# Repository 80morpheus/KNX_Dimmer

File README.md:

# KNX Dimmer
up to 16 channels possible
depends on the configuration

W = Single
CW = Cold/Warm White
RGB = RGB
RGBW = RGB+White
RGBCW = RGB+Cold/Warm White

Possible outputs:
3X  RGBCW
or
4x  RGBW
or
5X  RGB
or
8X  CW
or
16X W

CH1  S CW RGB RGBW RGBCW 
CH2  S CW RGB RGBW RGBCW 
CH3  S CW RGB RGBW RGBCW 
CH4  S CW RGB RGBW  
CH5  S CW RGB  
CH6  S CW      
CH7  S CW      
CH8  S CW      
CH9  S        
CH10 S        
CH11 S        
CH12 S        
CH13 S        
CH14 S        
CH15 S        
CH16 S         

# dimm bedingung
wenn abs oder rel dimmen dann nur bis min wert
wenn ausschalten, dann aus und optional farbwerte auf standard zurück setzen

single ist easy -> zwischen min und max

cw -> ginge auch zwischen min und max
      cw werte ??? müßte zwei min um evtl aus zu vermeiden
      ets eingabe farbtemp für c + w
      ets regler für temperatur gibt prozentual an welche der beiden wo steht
      links = nur c wird gesteuert und w ist dann 0
      mitte = beide selber wert
      rechts = nur w wird gesteuert und c ist dann 0

rgb -> dimmt nur von 0 bis setpoint
      min wert macht keinen sinn da dann zu komplizierte berechnungen

rgbw -> siehe rgb
      wie wird w behandelt ??? einzelnes licht objekt

rgbcw -> wie wird c und w behandelt ??? einzelnes licht objekt
      ets eingabe farbtemp für c + w
      ets standard wert - wird nach aus wieder aktiv ja/nein
      rgb dimmt von 0 bis setpoint

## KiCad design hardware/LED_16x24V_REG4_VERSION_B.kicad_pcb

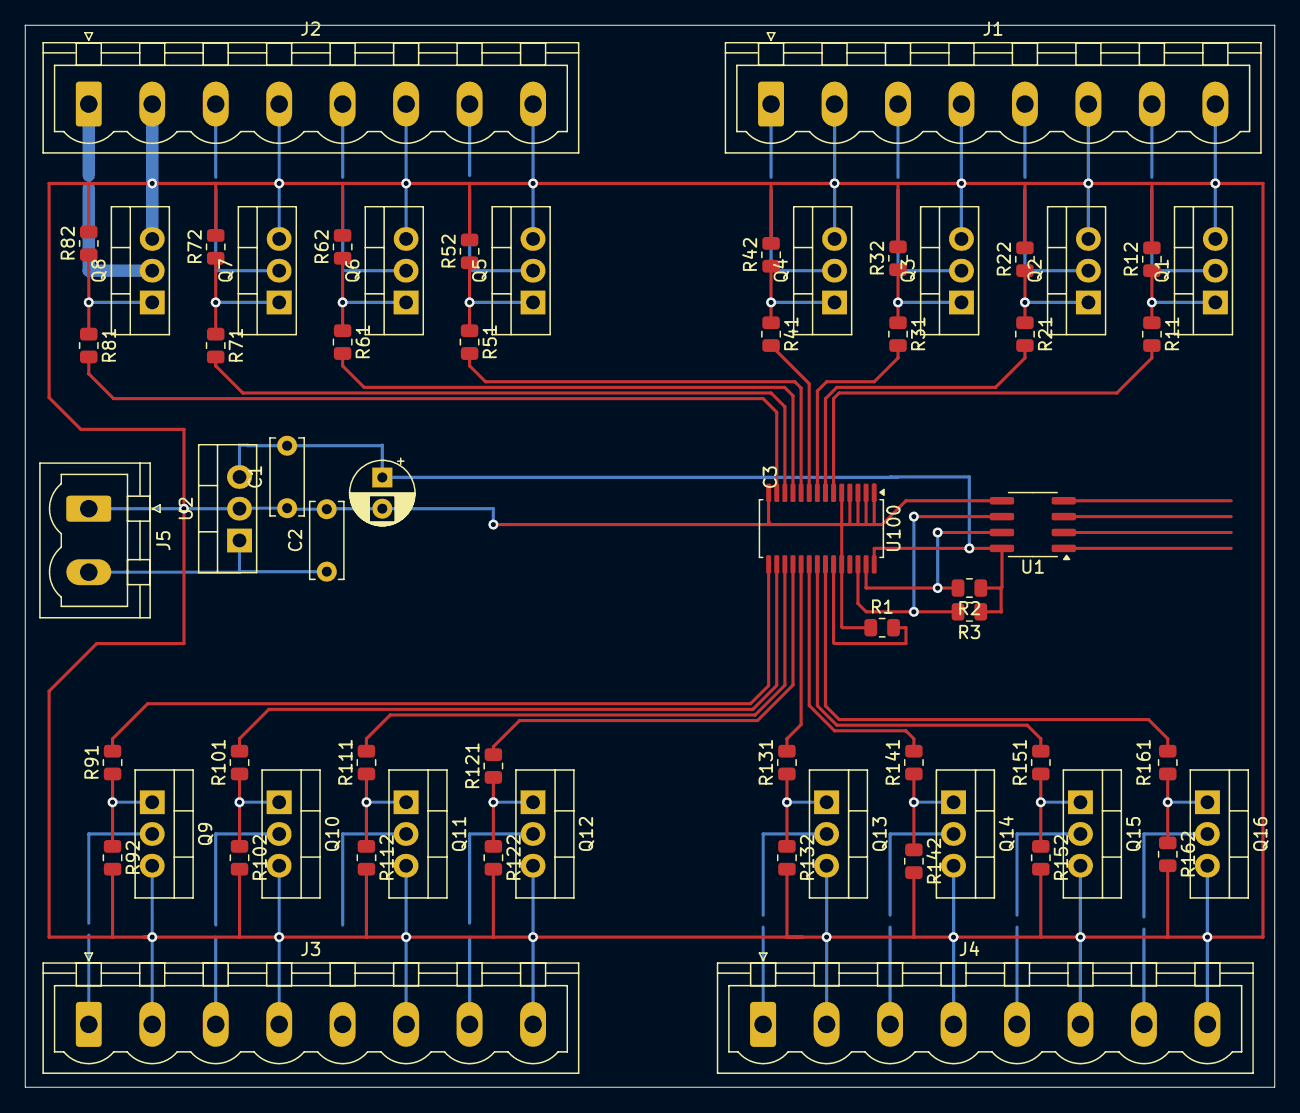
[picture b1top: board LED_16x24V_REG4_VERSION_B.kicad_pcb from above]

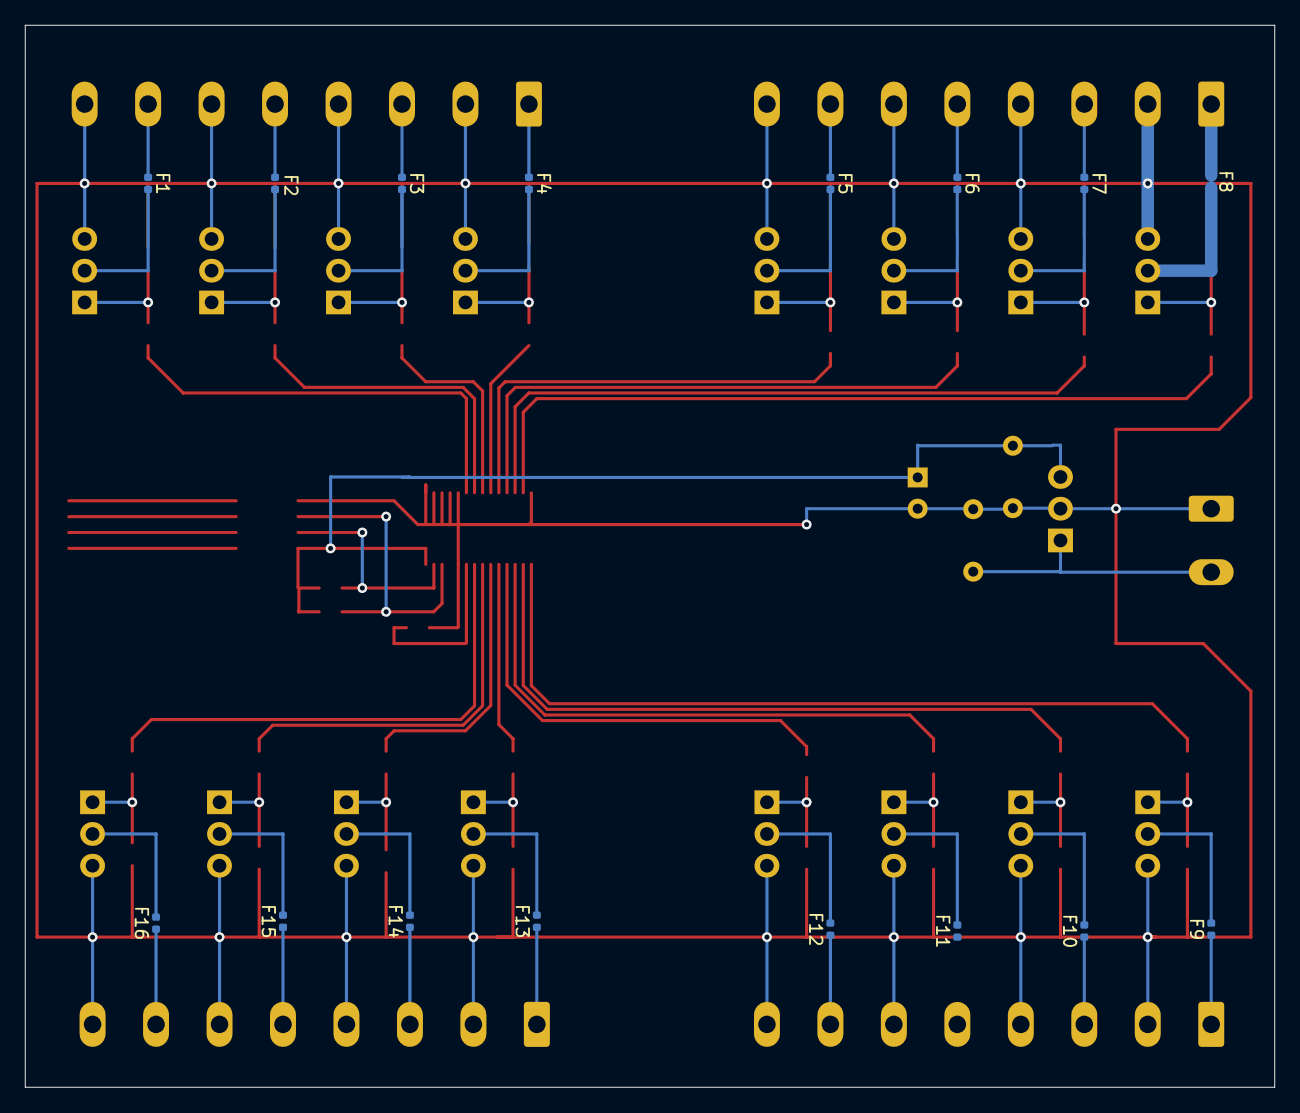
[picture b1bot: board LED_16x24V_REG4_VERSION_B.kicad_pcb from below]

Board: 2 copper layers, 100.0 x 85.0 mm, 78 parts (16 on the bottom side), 66 nets.

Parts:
C1: 0.1µF; C_Disc_D6.0mm_W2.5mm_P5.00mm
C2: 0.33µF; C_Disc_D6.0mm_W2.5mm_P5.00mm
C3: 100µF; CP_Radial_D5.0mm_P2.50mm
F1, F2, F3, F4, F5, F6, F7, F8, F9, F10, F11, F12, F13, F14, F15, F16: Fuse; Fuse_0402_1005Metric
J1, J2, J3, J4: Conn_01x08; PhoenixContact_MSTBVA_2,5_8-G-5,08_1x08_P5.08mm_Vertical
J5: Conn_01x02; PhoenixContact_MSTBVA_2,5_2-G-5,08_1x02_P5.08mm_Vertical
Q1, Q2, Q3, Q4, Q5, Q6, Q7, Q8, Q9, Q10, Q11, Q12, Q13, Q14, Q15, Q16: IRF3205; TO-220-3_Vertical
R1, R11, R12, R21, R22, R31, R32, R41, R42, R51, R52, R61, R62, R71, R72, R81, R82, R91, R92, R101, R102, R111, R112, R121, R122, R131, R132, R141, R142, R151, R152, R161, R162: R; R_0805_2012Metric
R2, R3: 10k; R_0805_2012Metric
U1: ADuM1250; SOIC-8_3.9x4.9mm_P1.27mm
U2: L7806; TO-220-3_Vertical
U100: PCA9685PW; TSSOP-28_4.4x9.7mm_P0.65mm

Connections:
GND_LED: C1.1, C2.2, C3.2, F7.1, F7.2, F8.1, F8.2, J1.2, J1.4, J1.6, J1.8, J2.1, J2.2, J2.3, J2.4, J2.6, J2.8, J3.2, J3.4, J3.6, J3.8, J4.2, J4.4, J4.6, J4.8, J5.1, Q1.3 (S), Q2.3 (S), Q3.3 (S), Q4.3 (S), Q5.3 (S), Q6.3 (S), Q7.2 (D), Q7.3 (S), Q8.2 (D), Q8.3 (S), Q9.3 (S), Q10.3 (S), Q11.3 (S), Q12.3 (S), Q13.3 (S), Q14.3 (S), Q15.3 (S), Q16.3 (S), R1.1, R12.2, R22.2, R32.2, R42.2, R52.2, R62.2, R72.2, R82.2, R92.2, R102.2, R112.2, R122.2, R132.2, R142.2, R152.2, R162.2, U1.5 (GND2), U2.2 (GND), U100.1 (A0), U100.2 (A1), U100.3 (A2), U100.4 (A3), U100.5 (A4), U100.14 (VSS), U100.24 (A5)
unnamed: F4.1, J1.1
unnamed: F3.1, J1.3
unnamed: F2.1, J1.5
unnamed: F1.1, J1.7
unnamed: F6.1, J2.5
unnamed: F5.1, J2.7
unnamed: F9.1, J3.1
unnamed: F10.1, J3.3
unnamed: F11.1, J3.5
unnamed: F12.1, J3.7
unnamed: F13.1, J4.1
unnamed: F14.1, J4.3
unnamed: F15.1, J4.5
unnamed: F16.1, J4.7
unnamed: C2.1, J5.2, U2.1 (IN)
unnamed: F1.2, Q1.2 (D)
unnamed: Q1.1 (G), R11.1, R12.1
unnamed: F2.2, Q2.2 (D)
unnamed: Q2.1 (G), R21.1, R22.1
unnamed: F3.2, Q3.2 (D)
unnamed: Q3.1 (G), R31.1, R32.1
unnamed: F4.2, Q4.2 (D)
unnamed: Q4.1 (G), R41.1, R42.1
unnamed: F5.2, Q5.2 (D)
unnamed: Q5.1 (G), R51.1, R52.1
unnamed: F6.2, Q6.2 (D)
unnamed: Q6.1 (G), R61.1, R62.1
unnamed: Q7.1 (G), R71.1, R72.1
unnamed: Q8.1 (G), R81.1, R82.1
unnamed: F9.2, Q9.2 (D)
unnamed: Q9.1 (G), R91.1, R92.1
unnamed: F10.2, Q10.2 (D)
unnamed: Q10.1 (G), R101.1, R102.1
unnamed: F11.2, Q11.2 (D)
unnamed: Q11.1 (G), R111.1, R112.1
unnamed: F12.2, Q12.2 (D)
unnamed: Q12.1 (G), R121.1, R122.1
unnamed: F13.2, Q13.2 (D)
unnamed: Q13.1 (G), R131.1, R132.1
unnamed: F14.2, Q14.2 (D)
unnamed: Q14.1 (G), R141.1, R142.1
unnamed: F15.2, Q15.2 (D)
unnamed: Q15.1 (G), R151.1, R152.1
unnamed: F16.2, Q16.2 (D)
unnamed: Q16.1 (G), R161.1, R162.1
unnamed: R3.2, U1.6 (SCL2), U100.26 (SCL)
unnamed: R2.2, U1.7 (SDA2), U100.27 (SDA)
unnamed: C1.2, C3.1, R2.1, R3.1, U1.8 (VDD2), U2.3 (OUT), U100.28 (VDD)
unnamed: R11.2, U100.6 (LED0)
unnamed: R21.2, U100.7 (LED1)
unnamed: R31.2, U100.8 (LED2)
unnamed: R41.2, U100.9 (LED3)
unnamed: R51.2, U100.10 (LED4)
unnamed: R61.2, U100.11 (LED5)
unnamed: R71.2, U100.12 (LED6)
unnamed: R81.2, U100.13 (LED7)
unnamed: R91.2, U100.15 (LED8)
unnamed: R101.2, U100.16 (LED9)
unnamed: R111.2, U100.17 (LED10)
unnamed: R121.2, U100.18 (LED11)
unnamed: R131.2, U100.19 (LED12)
unnamed: R141.2, U100.20 (LED13)
unnamed: R151.2, U100.21 (LED14)
unnamed: R161.2, U100.22 (LED15)
unnamed: R1.2, U100.23 (~OE)

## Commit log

2024-10-20 Create test
